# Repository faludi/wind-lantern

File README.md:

# Wind Lantern

A Wi-Fi-connected lantern whose LED flicker responds to local wind conditions. The firmware runs on a Raspberry Pi Pico W using MicroPython. This project is part of [Natural Electronics](https://wabitronics.com).

## Architecture

- `main.py` starts the firmware, reads local settings, connects to Wi-Fi, and runs the weather/settings update loop alongside the candle-light thread.
- `nature_api.py` provides Wi-Fi setup, location lookup, time synchronization, and weather requests. Wind speed and gust data come from Open-Meteo.
- `weather_service.py` fetches current wind readings and normalizes timestamps and speed units for the firmware.
- `clock_service.py` coordinates NTP synchronization and the cached lantern-local timezone offset used by night mode.
- `runtime_schedule.py` tracks settings, periodic-work, and time-sync deadlines using MicroPython tick semantics.
- `wind_manager.py` contains the wind/gust simulation shared by firmware and the hardware simulator.
- `lantern_hardware.py` owns the LED pin mapping, PWM setup, and Wi-Fi setup-button input.
- `lantern_config.py` defines firmware defaults and normalizes settings from local configuration and the server.
- `settings_store.py` loads and saves normalized settings in `config.json`.
- `settings_state.py` owns the normalized runtime settings and applies partial updates.
- `html/` contains the PHP dashboard and MySQL schema. The dashboard manages lantern accounts and settings.
- `html/settings_schema.php` defines dashboard metadata and the typed settings payload returned to firmware.
- `html/settings_actions.php` validates settings submissions and persists them after the dashboard checks login and CSRF.
- `html/admin_actions.php` handles administrator account, lantern registration, user update, and firmware-queue actions.
- `html/wind_data.php` fetches geocoding and current weather data for the dashboard's wind/map view.
- `html/lantern_checkin.php` identifies an active lantern by its Wi-Fi MAC address and returns its current settings and any queued firmware-update request.

The settings flow is:

1. Firmware defaults are defined in `lantern_config.py`.
2. At startup, the device loads and normalizes `config.json`.
3. The device periodically checks in with the configured settings endpoint. Valid remote values update the local settings; invalid or missing values keep their current fallback.
4. The resulting settings are saved to `config.json` when they change.

If the server cannot be reached, the device continues using its local settings. The firmware also refreshes weather data periodically and uses the configured address to resolve its location and timezone.

## Device Setup

1. Install MicroPython on the Pico W and copy the firmware modules from this repository to the device. `main.py` is the startup module.
2. Copy `secrets-example.py` to `secrets.py` and set `WIFI_SSID` and `WIFI_PASSWORD`. Keep the completed `secrets.py` out of source control.
3. To provision Wi-Fi without editing `secrets.py`, hold the setup button low on GP16 while the device starts. Join the `WindLantern-Setup-<last-four-MAC>` access point and submit the network credentials. The setup portal is open and times out after ten minutes.
4. For the multi-lantern dashboard and database setup, follow [testing/setup.md](testing/setup.md).

## Development Checks

The host test suite requires Python 3 and PHP CLI for cross-layer settings checks:

```sh
python3 -m unittest discover -s testing -v
php testing/test_settings_actions.php
php testing/test_admin_actions.php
```

The hardware simulator in `testing/lantern_test.py` requires a MicroPython environment and the lantern hardware connected. The host test suite does not require a Pico.

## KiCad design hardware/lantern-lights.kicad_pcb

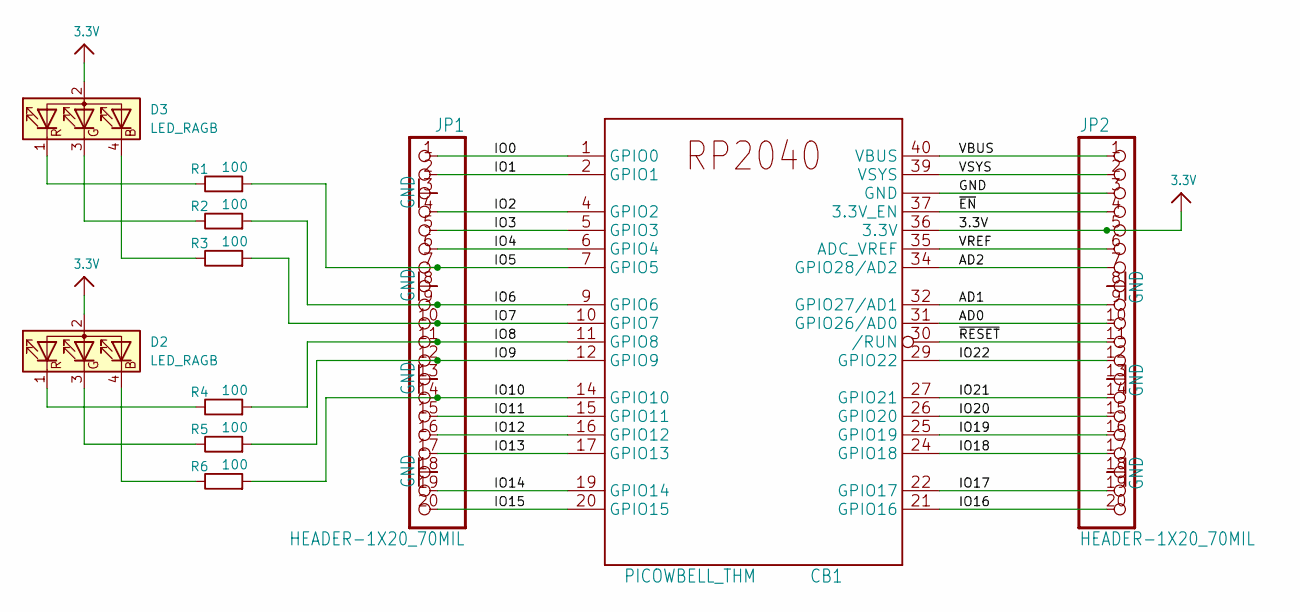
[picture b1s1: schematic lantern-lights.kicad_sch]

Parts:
CB1: PICOWBELL_THM; PICOWBELL
D2, D3: LED_RAGB; LED_D5.0mm-4_RGB
JP1, JP2: HEADER-1X20_70MIL; 1X20_ROUND_70MIL
R1, R2, R3, R4, R5, R6: 100; R_0805_2012Metric_Pad1.20x1.40mm_HandSolder; LCSC C4310

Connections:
3.3V: CB1.36 (3.3V), D2.2 (A), D3.2 (A), JP2.5
/AD0: CB1.31 (GPIO26/AD0), JP2.10
/AD1: CB1.32 (GPIO27/AD1), JP2.9
/AD2: CB1.34 (GPIO28/AD2), JP2.7
/IO0: CB1.1 (GPIO0), JP1.1
/IO1: CB1.2 (GPIO1), JP1.2
/IO2: CB1.4 (GPIO2), JP1.4
/IO3: CB1.5 (GPIO3), JP1.5
/IO4: CB1.6 (GPIO4), JP1.6
/IO5: CB1.7 (GPIO5), JP1.7, R1.2
/IO6: CB1.9 (GPIO6), JP1.9, R2.2
/IO7: CB1.10 (GPIO7), JP1.10, R3.2
/IO8: CB1.11 (GPIO8), JP1.11, R4.2
/IO9: CB1.12 (GPIO9), JP1.12, R5.2
/IO10: CB1.14 (GPIO10), JP1.14, R6.2
/IO11: CB1.15 (GPIO11), JP1.15
/IO12: CB1.16 (GPIO12), JP1.16
/IO13: CB1.17 (GPIO13), JP1.17
/IO14: CB1.19 (GPIO14), JP1.19
/IO15: CB1.20 (GPIO15), JP1.20
/IO16: CB1.21 (GPIO16), JP2.20
/IO17: CB1.22 (GPIO17), JP2.19
/IO18: CB1.24 (GPIO18), JP2.17
/IO19: CB1.25 (GPIO19), JP2.16
/IO20: CB1.26 (GPIO20), JP2.15
/IO21: CB1.27 (GPIO21), JP2.14
/IO22: CB1.29 (GPIO22), JP2.12
/VBUS: CB1.40 (VBUS), JP2.1
/VREF: CB1.35 (ADC_VREF), JP2.6
/VSYS: CB1.39 (VSYS), JP2.2
/~EN: CB1.37 (3.3V_EN), JP2.4
/~RESET: CB1.30 (/RUN), JP2.11
GND: CB1.3 (GND), CB1.8 (GND), CB1.13 (GND), CB1.18 (GND), CB1.23 (GND), CB1.28 (GND), CB1.33 (GND), CB1.38 (GND), JP1.3, JP1.8, JP1.13, JP1.18, JP2.3, JP2.8, JP2.13, JP2.18
unnamed: D2.4 (BK), R6.1
unnamed: D2.3 (GK), R5.1
unnamed: D2.1 (RK), R4.1
unnamed: D3.4 (BK), R3.1
unnamed: D3.3 (GK), R2.1
unnamed: D3.1 (RK), R1.1

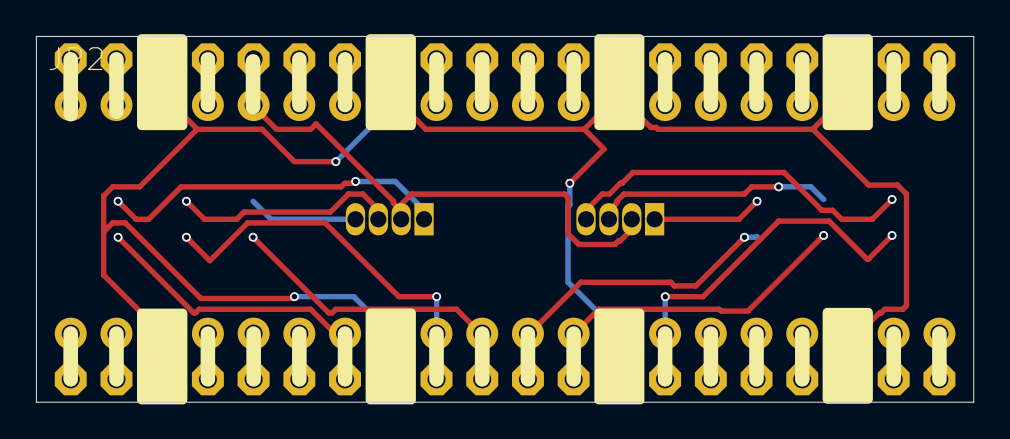
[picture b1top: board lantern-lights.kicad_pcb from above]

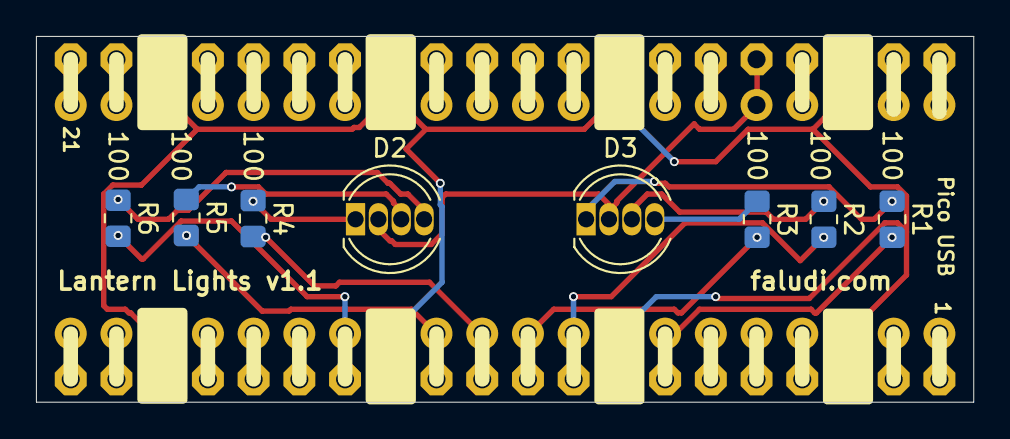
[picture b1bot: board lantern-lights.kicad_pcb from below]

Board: 2 copper layers, 52.1 x 20.3 mm, 11 parts (8 on the bottom side), 39 nets.

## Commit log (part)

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2025-09-26 remove dot files
2025-09-26 add link to readme
2025-09-26 format README.md for better readability
2025-09-30 gitignore add
2025-10-01 gitignore update
2025-10-01 add second core for lights
2025-10-01 multi-core version initial commit
2025-10-01 anemometer mode added
2025-10-02 remove troublesome irq and replace with polling plus thread locking
2025-10-07 add mode switch and garbage collection
2025-10-07 add watchdog to core 0
2025-10-25 WiFi wind lantern, separate settings and secrets files
2025-10-27 external config from server, basic
2025-10-28 online address update - basic
2025-10-29 call update location in function for repeatability
2025-10-30 Updates to PHP components
2025-10-30 update version number
2025-10-31 updates to adress parser and wind lookup online
2025-11-05 add error light output
2025-11-05 remove debugging printout
2025-11-10 store config as json and update
2025-11-11 save config and datetime
2025-11-20 reduced wind factor a bit
2025-11-26 Combine all online functions into a single page.
2025-12-05 Updates to settings for more dynamic display, even when wind is light. Changes to html text.
2026-01-20 add wind factor multiplier setting
2026-01-30 improve ntp call to handle exceptions and reduce frequency
2026-03-03 update wind factor multiplier
2026-03-09 reduce wind factor for better display
2026-03-27 add non-linear wind factors
2026-05-02 add watchdog to main loop
2026-05-02 update version
2026-05-16 incorporate nature_api
2026-05-26 Add new Nature API version
2026-06-16 update to new nature api
2026-06-20 update to use sync_time instead of ntptime for reliability
